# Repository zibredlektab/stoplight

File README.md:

# stoplight
P-Tap voltage meter stoplight

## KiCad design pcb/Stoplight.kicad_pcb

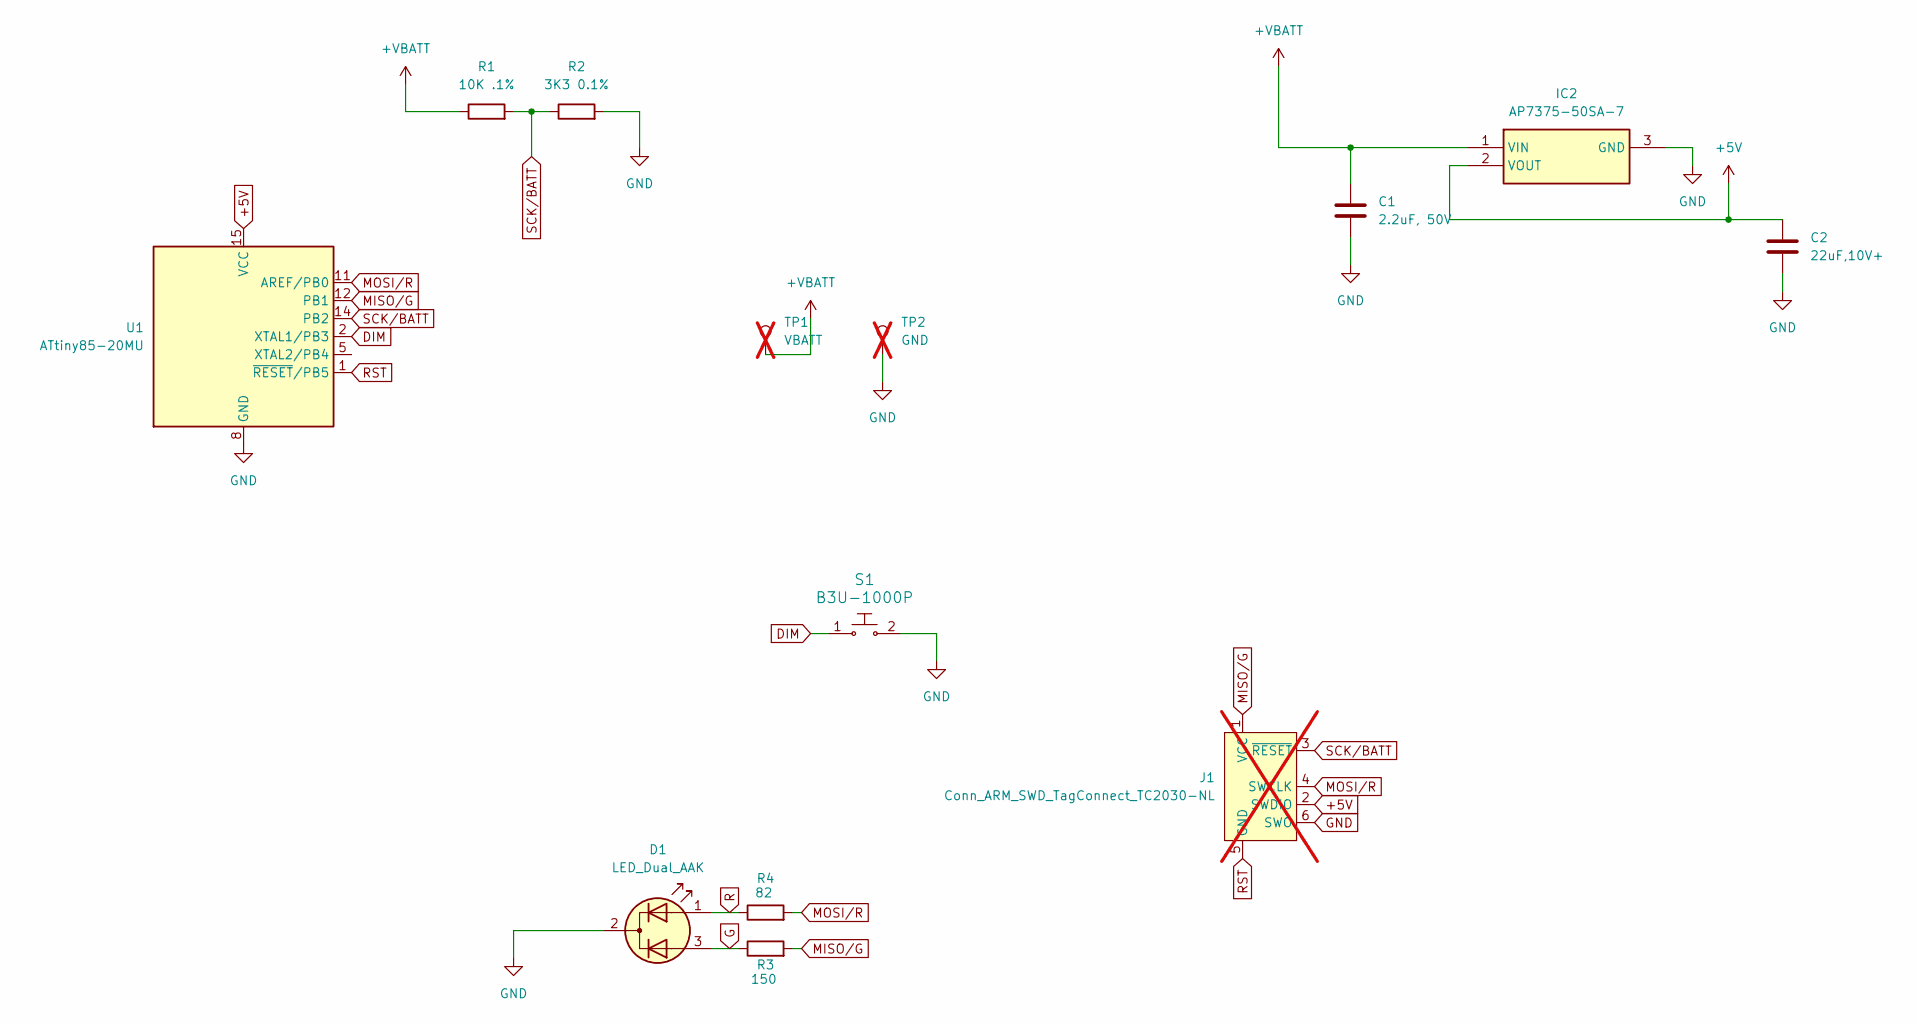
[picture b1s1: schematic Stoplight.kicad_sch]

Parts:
C1: 2.2uF, 50V; C_0603_1608Metric; Part Number GRM188R61H225KE11D
C2: 22uF,10V+; C_0402_1005Metric; Part Number GMC04X5R226M10NT
D1: LED_Dual_AAK; LED_D5.0mm-3; Part Number WP59SURKZGW
IC2: AP7375-50SA-7; TSOT-23; Part Number AP7375-50SA-7
J1: Conn_ARM_SWD_TagConnect_TC2030-NL; Tag-Connect_TC2030-IDC-NL_2x03_P1.27mm_Vertical; not fitted
R1: 10K .1%; R_0402_1005Metric; Part Number 4-2176755-8
R2: 3K3 0.1%; R_0402_1005Metric; Part Number TNPW04023K30BEED
R3: 150; R_0402_1005Metric; Part Number ERJ-PA2F1500X
R4: 82; R_0402_1005Metric; Part Number ERJ-PA2F82R0X
S1: B3U-1000P; Switch_Tactile_SMD_B3U-1000P; Part Number B3U-1000P
TP1: VBATT; TestPoint_Pad_2.0x2.0mm; not fitted
TP2: GND; TestPoint_Pad_2.0x2.0mm; not fitted
U1: ATtiny85-20MU; QFN-20-1EP_4x4mm_P0.5mm_EP2.6x2.6mm; Part Number ATTINY85-20MU

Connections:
+5V: C2.2, IC2.2 (VOUT), J1.2 (SWDIO), U1.15 (VCC)
+VBATT: C1.2, IC2.1 (VIN), R1.1, TP1.1
DIM: S1.1, U1.2 (XTAL1/PB3)
G: D1.3 (A2), R3.1
GND: C1.1, C2.1, D1.2 (K), IC2.3 (GND), J1.6 (SWO), R2.2, S1.2, TP2.1, U1.8 (GND), U1.21 (GND)
MISO/G: J1.1 (VCC), R3.2, U1.12 (PB1)
MOSI/R: J1.4 (SWCLK), R4.2, U1.11 (AREF/PB0)
R: D1.1 (A1), R4.1
RST: J1.5 (GND), U1.1 (~RESET/PB5)
SCK/BATT: J1.3 (~RESET), R1.2, R2.1, U1.14 (PB2)

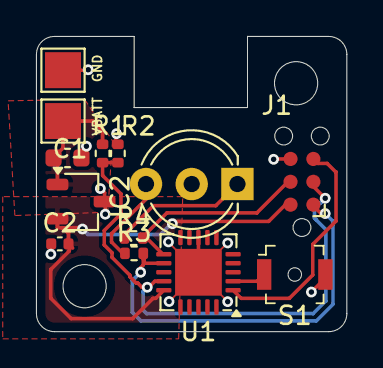
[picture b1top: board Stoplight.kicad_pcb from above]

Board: 2 copper layers, 17.2 x 16.4 mm, 13 parts (0 on the bottom side), 10 nets.

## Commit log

2025-03-02 initial pcb work
2025-03-03 Started coding
2025-03-03 Good double-sided design
2025-03-03 Tested on breadboard, working
    calibrated voltage levels
2025-03-03 Added dimming
2025-03-04 Another solid design, but going to try for even simpler
2025-03-04 Almost entirely single-layer now
2025-03-06 Added hysteresis for increasing voltage levels, pretty solid now
2025-03-06 some rearranging
2025-03-11 Swapped mcu package to SOIC-8 for easier soldering
2025-03-11 Code now properly calculates voltage from ADC
2025-03-18 Ordered v1, updated part numbers to reflect availability
2025-08-26 pcb v1a
2025-09-15 Replaced dimmer with dim button. Currently functional
2025-09-16 redesigning pcb to be smaller & use tag-connect
2025-09-16 pcb v1b, ready to manufacture
2025-09-24 v1b PCB as ordered
2026-04-10 Updated code to reflect wiring changes in v1b
